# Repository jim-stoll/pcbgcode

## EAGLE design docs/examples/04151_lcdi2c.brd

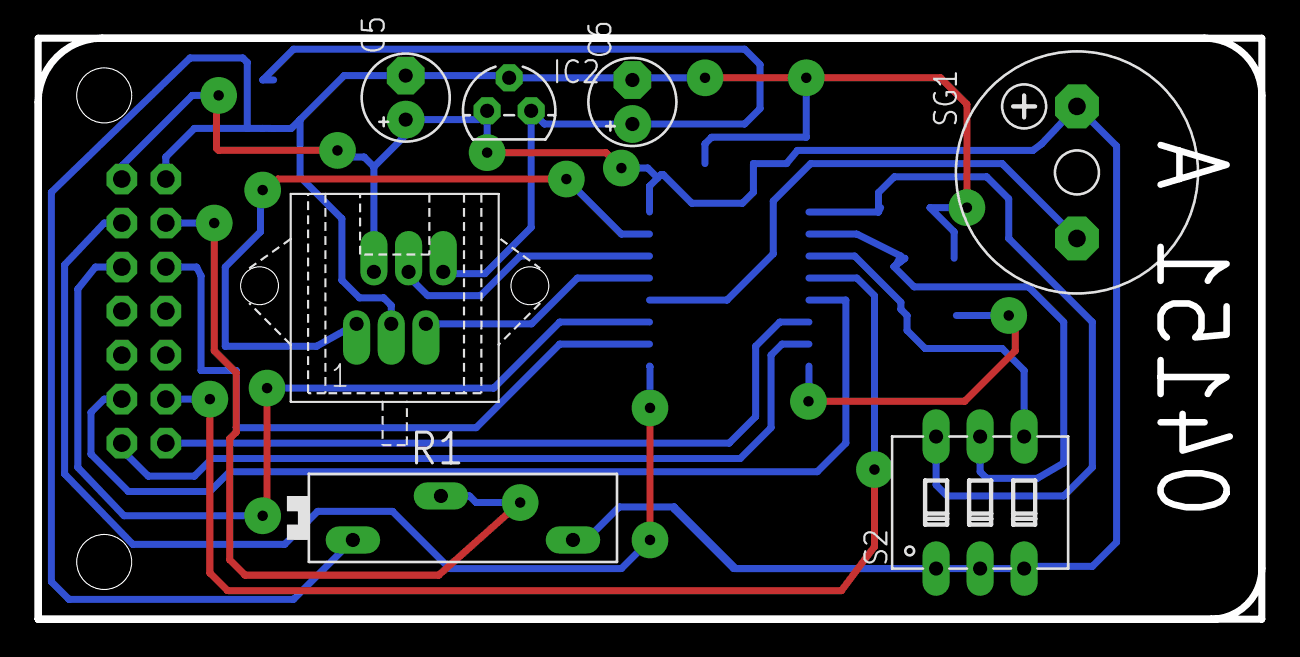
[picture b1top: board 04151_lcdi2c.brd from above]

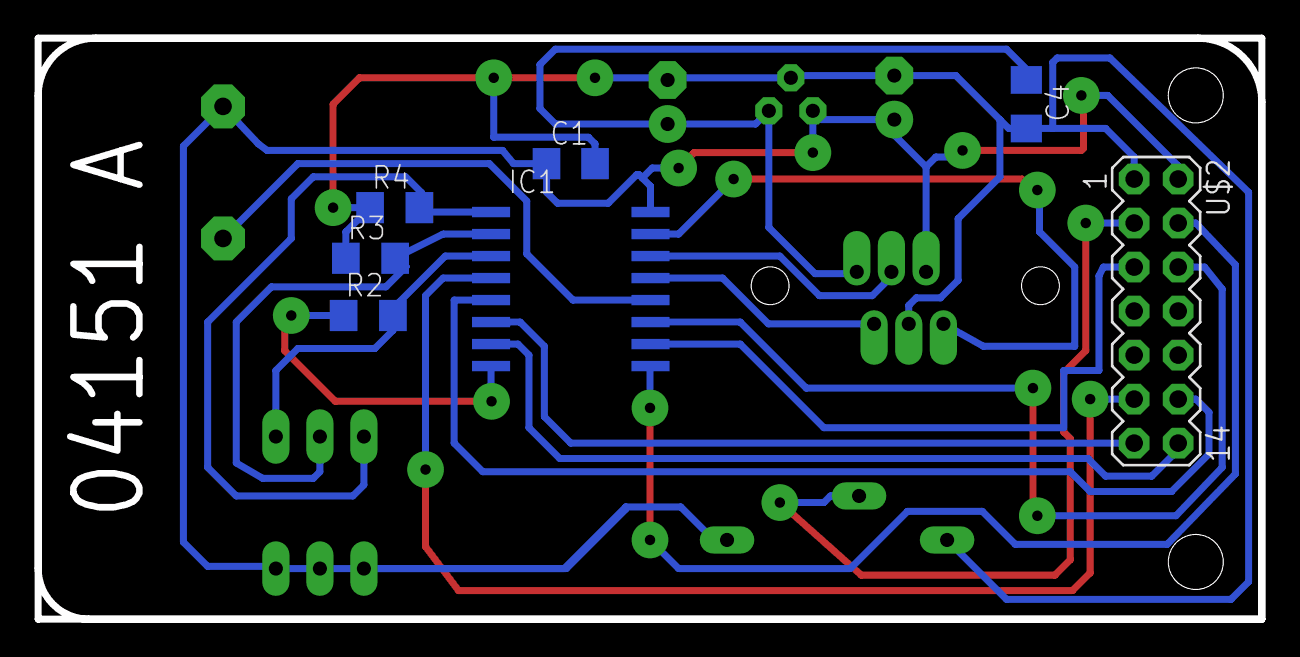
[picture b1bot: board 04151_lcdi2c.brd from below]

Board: 2 copper layers, 70.6 x 33.5 mm, 14 parts (7 on the bottom side), 18 nets.

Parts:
C1, C4: 100nf; C1206
C5, C6: !FAT_E2,5-5
IC1: PCF8574T; SO16W
IC2: 78L05Z; TO92
R1: PT-SPIN
R2, R3, R4: R1206
S2: DIP03YL
SG1: F/CM12P
U$1: RJ-12
U$2: MA07-2-SGL; MA07-2

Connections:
D4: IC1.4, U$2.11
D5: IC1.5, U$2.12
D6: IC1.6, U$2.13
D7: IC1.7, U$2.14
E: IC1.11, U$2.6
GND: C1.2, C4.2, C5.P$2, C6.P$2, IC1.8, IC2.2, R1.A, R2.1, R3.1, R4.1, U$1.3_GND, U$2.1
unnamed: R1.S, U$2.3
unnamed: IC1.3, R2.2, S2.4
unnamed: IC1.2, R3.2, S2.5
unnamed: IC1.1, R4.2, S2.6
unnamed: IC1.13, U$1.5_INT
unnamed: IC1.15, U$1.1_SDA
unnamed: IC1.12, SG1.-
unnamed: IC1.14, U$1.4_SCL
unnamed: C4.1, C6.P$1, IC2.3, U$1.6_VAUX
RS: IC1.9, U$2.4
RW: IC1.10, U$2.5
VCC: C1.1, C5.P$1, IC1.16, IC2.1, R1.E, S2.1, S2.2, S2.3, SG1.+, U$1.2_VCC, U$2.2

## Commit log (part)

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2012-12-16 Initial commit of 3.5.2.11 to the trunk.
2012-12-17 Branching to create maintenance release.
2012-12-17 Changed math.h to work with Eagle 5 or 6. Updated math.ulp to perform more tests on math.h to ensure conversions work correctly.
    Removed progress menu options in pcb-gcode-setup.ulp, as no one uses them, and it can confuse new users.
    Changed Isolation|Default label to Minimum. Globally changed DEFAULT_ISOLATE variable to ISO_MIN.
    Added a drill sub for the examples/04151_lcdi2c.drl file so it wouldn't complain about the 0.086in drill.
    Added name of drill rack file to drill not found message in drill.h.
    Added a Single pass option. Maximum and Step size labels are changed to "not used" when Single pass is on.
    The path to pcb-gcode is no longer required to be entered in Eagle's Control Panel
2012-12-17 Made g_path check error message more descriptive, and now bails out if pcb-gcode can't locate itself.
2012-12-17 Fixed typo in rakefile.
2012-12-17 The viewer now defaults to color. Added copyright message.
2012-12-17 Fixed viewers.
2012-12-17 Changes after test run.
2012-12-26 Prep for new release.
2012-12-29 Branching trunk to 3.6.0.2.
2012-12-29 Copied in all files from the development folder for the manual.
2012-12-29 Old docs removed. New docs copied in. Untested.
2012-12-29 Somehow make/write_convert_units.rb had been removed. Copied it from 3.3 and fixed it to work with the new conversion routine. It now removes the pcb-gcode-setup.old file it left around too.
2012-12-29 Added :write_convert_units task to the default task. Also, a task was added to check if the build is occuring in a folder with .svn files, and if so, abort. This to avoid the loads of .svn files in t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
2012-12-29 Now omits the make directory in addition to its contents.
2012-12-29 Fixed a typo in the rakefile.
2012-12-29 Implemented argv[0] suggestion from MC Cason.
2012-12-29 Trying to ignore backup files ending in .?##
2013-01-02 The docs/figs/* files are now omitted from the .zip file to save about 2MB.
2013-01-02 Zip builder now assumes files are in pcb-gcode-version folder so that the folder name can be included in the archive.
2013-01-02 Zip builder now creates a temp .zip file, unzips into pcb-gcode-version, then creates the release .zip file from there. Bumped version number in pcb-gcode
2013-01-09 Removed path stuff I broke on a suggestion. Pcb-gcode now has to be in the Options | Directories | ULP field again.
2013-01-09 Branching, a bit late.
2013-01-09 Updated version number in manual.
2013-01-09 Updated version in rakefile.
2013-01-17 Forgot to bump version numbers in .ulps.
2013-01-27 Updated version number throughout.
2013-09-18 Added supporters to the manual. Added notes about Windows installation and the previewer.
2013-11-28 When tool change with zero step was on, the drill function was outputting another TOOL_CHANGE sequence after the initial TOOL_CHANGE, rather than just a pause for the operator to zero the bit. Fixed 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
2013-11-28 Added comment
2013-11-29 Needs to be tested thoroughly and have messages, etc. removed.
2013-11-29 Removed test messages, etc. Ready for Test #12
2013-11-29 Ignoring LaTeX intermediate files.
2013-11-29 Must be executable to be run from rakefile.
2013-11-29 Bumped version number.
2013-11-29 Sensible default options.
2013-11-29 Ignore Texpad temp files.
2013-11-29 Added code to ensure the first run through output_mill_code() results in a ST_START_LINE state.
2013-11-29 Added an initial rapid to DEFAULT_Z_HIGH before move to home to ensure tool is in a safe position.
2013-11-29 Calculation for center of arc was incorrect. Fixed #16
2013-11-29 Added drill preview utilizing spot drill mechanism. Drill preview is only available when spot drill is selected. Test #3
2013-11-29 Drill preview no longer requires spot drill to be enabled. Preview is shown on outline preview, so bottom and/or top outline is required to be on. Test #3
2013-12-03 Added support for saving and loading settings to files. Settings in pcb-default.h and pcb-machine.h are saved/loaded. Functionality appears in the Plugins tab. Test #9
2013-12-04 Cleaning up code and getting rid of detritus.
2013-12-04 Removed unused code that used to show a progress menu and optionally restore the user’s menu.
2013-12-06 Fixed unknown g_phase message when user gcode was turned on. re #22
2013-12-20 Side effect bug wherein the drill hole count was incremented due to asking for a tool number for a drill size. Changed sample rack file to eliminate complaints about 0.044” hole size in enabtmr board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
2013-12-20 Added spindle speed settings to setup program, one for etch, mill/text and drill. Test #25
2013-12-20 Renamed DEFAULT_WIDTH and other variables and constants that referred to ‘width’ to refer to tool size, which is more appropriate. Re #27
2013-12-22 Drill table not sorted properly. Added ‘numeric’ to the g_stack[] string statement, which should make it sort correctly. Test #24
2013-12-22 .release files updated to current content.
2013-12-22 Zero size drills are now ignored.
2013-12-22 Added reset of saved coordinates before beginning gcode output. Test #30
2013-12-22 Updated file to include new spindle speed settings.
2013-12-30 Current x, y, and z were not being updated for drill holes.
2013-12-30 Updated example files using new code. Test #33
2013-12-30 Tool numbers in drill rack files that did not start at T01 did not work. Test #34
2013-12-30 Bumped version to 3.6.1.1
2014-01-03 Now generates an error if no profiles are available, even if a path is found. No longer opens the overwrite caution window if the program has not been set up previously. Test #35
2014-01-11 Thanks for mentioning the R parameter, @brett_pound. Arcs now use the R parameter - much easier than trying to calculate offsets for I, J parameters. Sample files regenerated. Changes to all .pp file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
2014-01-12 Bumped version.
2014-01-12 Updated preview image in manual. Now has X’s for drill preview. Re #3
2014-01-12 Drill preview shown in etch preview is now only shown when drills for that side are turned on. I.e. no drill file, no preview of drill holes. Re #3
2014-01-12 Updated docs to reflect new use of the R parameter for arcs, and the change to the use of ARC_TOP and ARC_BOTTOM. Re #16
2014-01-12 Added docs for supporting multiples sets of settings. Re #9
2014-01-13 Updated supporters.
2014-01-14 Improved comments in generated files. Now, rather than the kitchen-sink all settings from the pcb-machine.h file, they comments include settings relevant to the file being generated. Test #27
2014-01-14 Implemented support for separate feed rates and spindle speeds for etching, milling, drilling, and text. Regenerated sample files. Removed redundant “save” message from save settings routine. Test #32
2014-01-14 Update docs. Updated docs and figure for the Machine tab. Re #32
2014-01-14 Incorrect feed rates used for arcs and Z moves before arcs. Re #32
2014-01-15 Moved redundant out_lines sets of commands into their own function.
2014-01-15 Created define for file mode text “wt” and “at”.
2014-01-15 Cleaned up unit of measure determination, ie. made it a function.
2014-01-15 Removed unused parameter suffix form write_outlines and drill routines.
2014-01-15 Ensured all functions and global code blocks have comments and they are valid.
2014-01-15 Updated comments.
2014-01-16 Number of passes wrong in preview. Test #38
2014-01-16 Corrected tool size / depth display. The previewer was displaying a tool size which was the milling depth. Now correctly displays “depth” and either the text or milling depth, as appropriate. Test #39
2014-01-16 Cleaned up and added comments.
2014-01-16 Text files were using mill spindle speeds. Copy and paste strikes again. Test #42
2014-01-16 Regened example files.
2014-02-05 Added cream stencil support
    PZ added support for milling cream stencils.
    Needs testing. Error @923 when bottom stencil turned on and SMD part on top layer only.
2014-02-05 Adding code to implement Peter's stencil cutting code.
2014-02-05 Fixed preview for stencil files.
2014-02-06 Changed some components to SMD to test new stencil functionality.
2014-02-06 Added layer check to prevent error. An error was being generated if, for example, an SMD part was on the bottom and the option to generate a top stencil was selected. Updated default saved settings s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
2014-02-06 Updated docs to include stencil info.
2014-02-06 Beta 3.6.1.6 release. Bumped version, built release files.
2014-02-06 Optimize generated milling g-code. Untested.
2014-02-06 Update profiles
    Change to ...CLOCK and ...CCLOCK wording.
2014-02-06 Optimize etching code.
    Untested.
2014-02-06 Add climb option to optimized etching. re: #43
2014-02-06 Removed debug code. re: #43
2014-02-06 Code cleanup. Added m_ prefix to all module level variables. Updated Martin's contribution in the docs. re: #43
2014-02-06 Added setunchanged batch file so git will ignore files that have irrelevant changes.
2014-02-06 Updated docs to show and explain the 'Prefer climb' option. re: #43
2014-02-06 Bumped version. Updated saved settings files.
2014-02-10 Update and improve index.
2014-02-10 No longer calls convert multiple times for variables used in the UI multiple times.
2014-02-10 UI cleanup and size reduction.
2014-02-10 Index entries added.
2014-02-10 Index additions.
2014-02-10 Removed 'Other' tab. Updated docs.
2014-02-13 Added index entries.
2014-03-19 Martin's fixes for the optimization hang bug. Re: #43
2014-03-19 Added operator message to be inserted into generated NC files. Re: #45
2014-03-19 Updated docs to show and explain new Operator Message capability. Re: #45
2014-03-19 Created 3.6.1.8 beta release.
2014-03-24 Added arc viewing functionality to previewer. Test #41
2014-03-25 Bumped rev for beta release. Regened manual.
2014-03-25 Changed drill depth to SPOT_DRILL_DEPTH and removed extraneous generated code. Test #47
2014-04-08 Updated docs re: javaw.exe on Windows. Added pour to top of 04151_lcdi2c.brd file. Exploded components and moved text off edge to prevent isolation rectangle from extending past board edges.
2014-04-11 Removed 'etching tool size' from Generation tab.
2014-04-11 Back to usual default file generation options.
2014-04-11 Update copyright year.
2014-04-11 Updated version numbers. Updated docs for removal of etching tool size from Generation tab. Updated docs to new version number.
2014-04-11 Files built for release of 3.6.2.0.
2014-04-13 Added width and height settings for the previewer window in pcb-gcode-setup. Test #51
2014-04-13 Updated version numbers. Updated saved settings files. Re: #51
2014-04-14 Tries to intelligently place the preview window based on width and height of screen and preview size requested. Re: #51
2014-04-14 Bumped rev to create test release for Macka.
2014-04-14 Updated donors. Replaced Fabrice's mom's name (Astrid Adam) with his.
2014-04-14 Autoleveller code based on Poul-Henning Kamp's code. Alpha, barely tested. Test: #11
2014-04-21 Line numbers required for sub calls. If probing is enabled, line numbers are now turned on automatically.
2014-04-29 Changed the units() and Peter's from_units() to use the existing convert() function from math.h which is compatible with both Eagle 5 and Eagle 6. Test #52
2014-04-29 Added version number update task to rake file.
2014-05-14 Added new donors.
2014-05-18 Replaced SPOT_DRILL_DEPTH with DRILL_DEPTH in the DRILL_HOLE command string. Test: #53
2014-05-18 Bumped version number. Created release. https://dl.dropboxusercontent.com/u/46579026/pcb-gcode-3.6.2.4.zip Fixed: #53
2014-05-18 Added offset parameters to the setup program under the Machine tab. Added a rapid to scale_x(0), scale_y(0) at the end of each file to facilitate moving to position for next board to be etched. Made 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
2014-05-20 Radius for curves was broken due to not being scaled on the bottom of the board. Test: #54
2014-05-20 User now has the option of using %s in the TOOL_CHANGE definition, rather than FORMAT. If %s is present, pcb-gcode will output the tool size as it appears in the rack file. Test: #56 Leading zeroes a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
2014-05-21 Added dropbox task to copy zip file to Dropbox folder.
